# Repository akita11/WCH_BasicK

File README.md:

# WCH_BasicK

## これは何？

- [中国のWCH社](http://www.wch-ic.com/)の格安USB-シリアル変換チップCH340Kを使った、USB-シリアル変換器です。
- Arduino等の書き込みやシリアル通信で、標準的に使われる[FTDI Basic](https://www.switch-science.com/catalog/342/)と同じ6ピンコネクタを備えています。
- PC側のコネクタはUSB Type-Cです。
- FTDI Basic互換の6ピンコネクタ以外に、ESP32の書き込み等で用いられるRTS#信号を、脇の端子に引き出してありますので、必要な場合はそこにコネクタ等を接続して利用できます。
- FTDI Basic互換の6ピンコネクタのVDD端子に供給される電圧は、5Vと3.3Vから選択できます。（初期設定は5V）

## 使い方

- （必要であれば同梱の6pソケットをはんだ付けします。）
- [WCH社のドライバのダウンロードサイト](http://www.wch-ic.com/search?q=CH340&t=downloads)から最新のドライバをインストールしておきます。※一部サイトで、古いバージョンのドライバへのリンクが貼られているところがあります。接続後のドライバのインストールに失敗する場合は、最新のドライバをインストールします。
- 市販のUSB Type-Cコネクタを持つケーブルでPCと接続し、ArduinoIDEのシリアルモニタ等のCOMポートを用いるアプリケーションから使用します。
- 【注意】送受信などの制御信号線のHレベルは5Vで固定です（次バージョンでVDDに連動するよう修正予定）

## 使い方（オプション）
- RTS#信号を使用する場合は、基板上のRTS#と示した箇所のランドを使用してください。なおその脇にはGND端子があります。
- 6pコネクタのVDD端子の供給電圧を初期設定の5Vから3.3Vに変更する場合は、裏面ソルダージャンパの「中央-5V間」をカッター等で切断し、「中央-3.3V間」をハンダで接続してください。または切り離した状態で、脇の3p端子にピンヘッダ等を取り付けて3.3V/5Vを切り替えられるようにしてください。
- USB Type-Cコネクタ脇の2組の2p端子は無接続です。ブレッドボード等に固定するヘッダピンを取り付けるなどに使用できます。

## （自作する方向け）作り方

- 基板データ(KiCAD)またはそこから生成したガーバーデータを使って、基板を製造します。
- 部品を入手します。
  - [CH340K](https://akizukidenshi.com/catalog/g/gI-16306/)
  - [USB Type-Cコネクタ](https://akizukidenshi.com/catalog/g/gC-14356/)
  - 0.1uFチップコンデンサ(1608サイズ)：：2個
  - 1kΩチップ抵抗(1608サイズ)
  - 5.1kΩチップ抵抗(1608サイズ)：2個
  - 緑チップLED(1608サイズ)
  - [350mAポリスイッチ(3216サイズ)](https://akizukidenshi.com/catalog/g/gP-13490/)
  - [ピンソケット6p](https://akizukidenshi.com/catalog/g/gC-03784/)
- 基板上に部品をとりつけます。

## Author

Junichi Akita (akita@ifdl.jp, @akita11)

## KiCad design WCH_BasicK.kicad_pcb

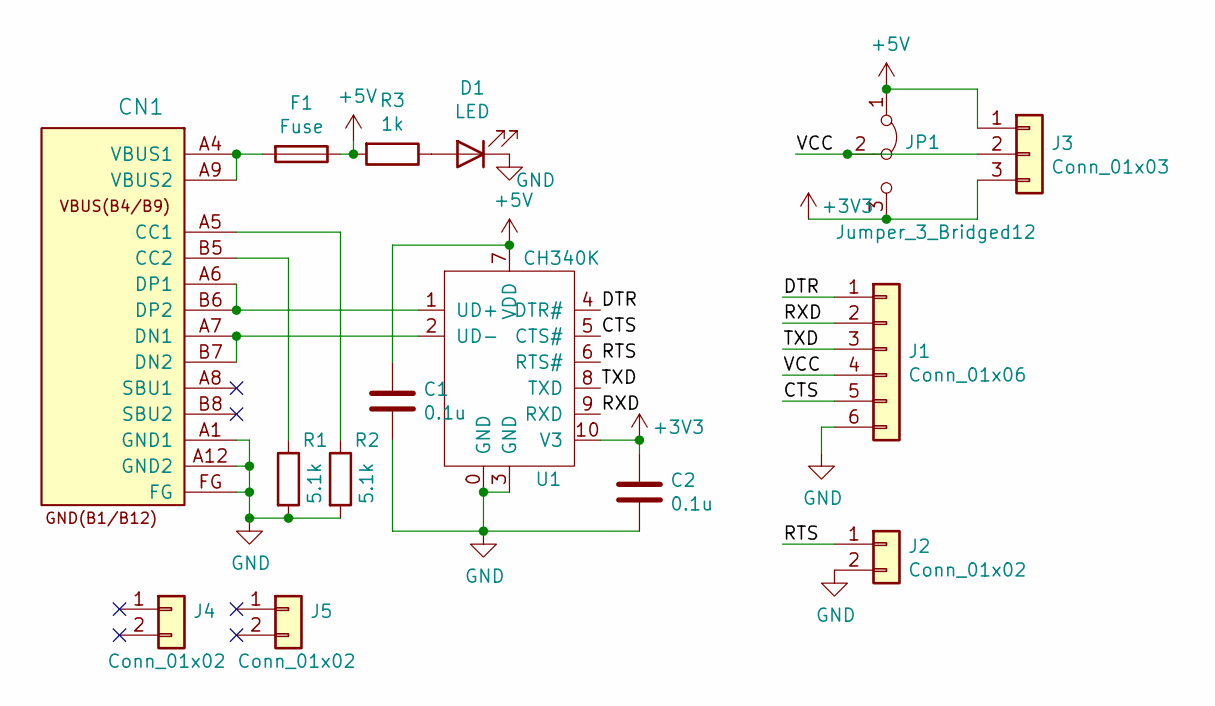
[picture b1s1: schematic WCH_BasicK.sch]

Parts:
C1, C2: 0.1u; C_0603_1608Metric
CN1: CON_USB-C-16; USB-C_16P_TH
D1: LED; LED_0603_1608Metric
F1: Fuse; Fuse_1206_3216Metric
J1: Conn_01x06; PinSocket_1x06_P2.54mm_Vertical
J2, J4, J5: Conn_01x02; PinSocket_1x02_P2.54mm_Vertical
J3: Conn_01x03; PinSocket_1x03_P2.54mm_Vertical
JP1: Jumper_3_Bridged12; SolderJumper-3_P1.3mm_Bridged2Bar12_Pad1.0x1.5mm
R1, R2: 5.1k; R_0603_1608Metric
R3: 1k; R_0603_1608Metric
U1: CH340K; ESOIC-10_P1.0mm

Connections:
+3V3: C2.1, J3.3, JP1.3 (B), U1.10 (V3)
+5V: C1.1, F1.1, J3.1, JP1.1 (A), R3.2, U1.7 (VDD)
/CTS: J1.5, U1.5 (CTS#)
/DTR: J1.1, U1.4 (DTR#)
/RTS: J2.1, U1.6 (RTS#)
/RXD: J1.2, U1.9 (RXD)
/TXD: J1.3, U1.8 (TXD)
/VCC: J1.4, J3.2, JP1.2 (C)
GND: C1.2, C2.2, CN1.A1 (GND1), CN1.A12 (GND2), CN1.FG, D1.1 (K), J1.6, J2.2, R1.2, R2.2, U1.0 (GND), U1.3 (GND)
unnamed: CN1.A4 (VBUS1), CN1.A9 (VBUS2), F1.2
unnamed: CN1.A5 (CC1), R2.1
unnamed: CN1.A6 (DP1), CN1.B6 (DP2), U1.1 (UD+)
unnamed: CN1.A7 (DN1), CN1.B7 (DN2), U1.2 (UD-)
unnamed: CN1.B5 (CC2), R1.1
unnamed: D1.2 (A), R3.1

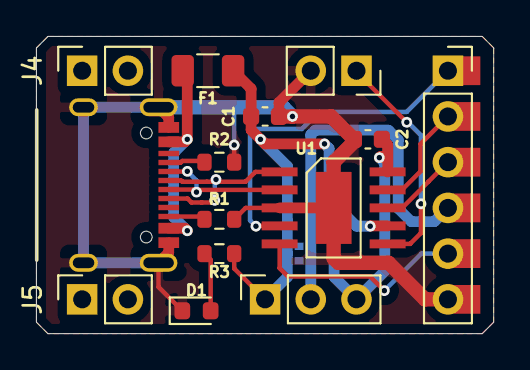
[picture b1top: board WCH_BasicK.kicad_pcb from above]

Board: 2 copper layers, 25.4 x 16.5 mm, 15 parts (1 on the bottom side), 15 nets.

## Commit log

2021-05-13 Add files via upload
    initial commit
2021-05-26 写真の追加
2021-05-26 README.mdのリンクを修正
